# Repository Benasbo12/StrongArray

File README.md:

# StrongArray
Strong array schematics and programs for use with MSc by research thesis - Benjamin Astbury

PySweeperGUI - ArduinoRev4 for use with controlling Raspberry Pi

Switch4x4 for uploading to Arduino Due

Eagle Schematics and board for production and fitting to top of Arduino Due as specified in Thesis

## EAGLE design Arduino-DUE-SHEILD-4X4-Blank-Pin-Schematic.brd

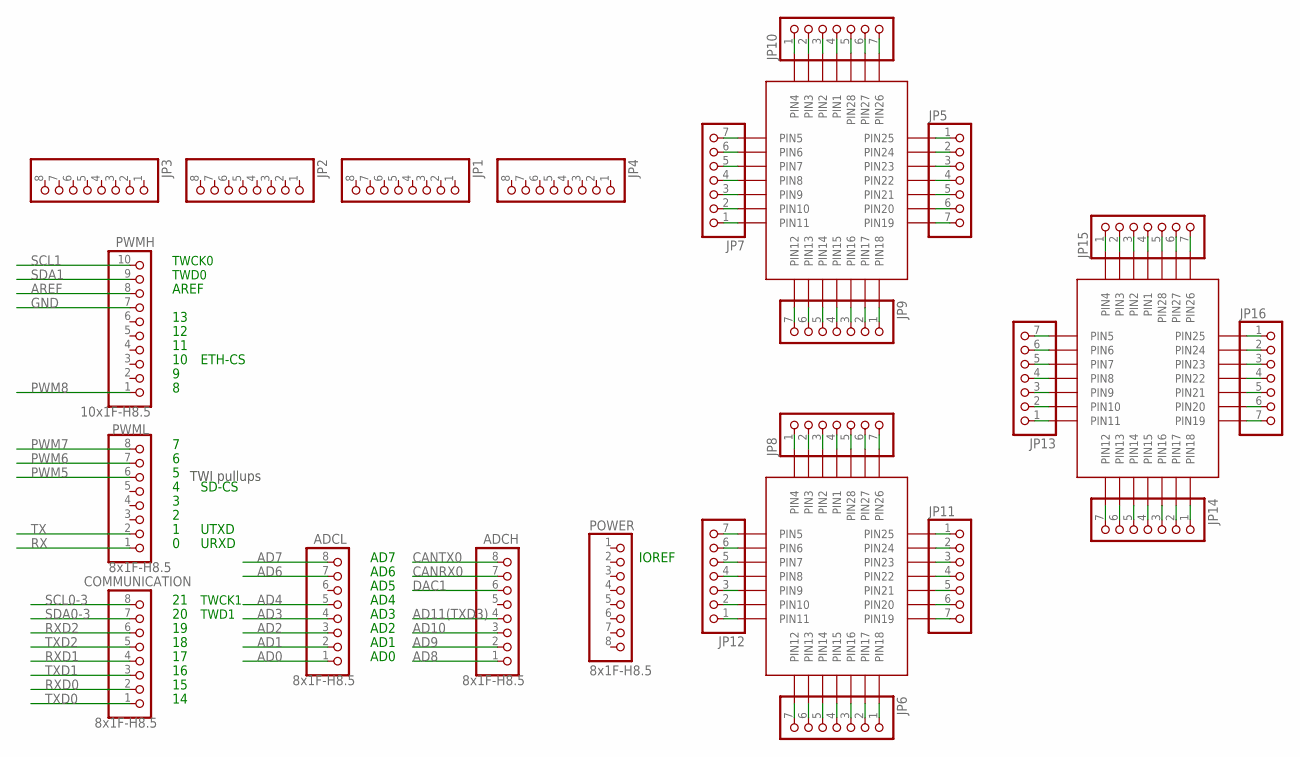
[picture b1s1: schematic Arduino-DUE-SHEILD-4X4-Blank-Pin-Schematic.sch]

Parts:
ADCH: 8x1F-H8.5; 1X08
ADCL: 8x1F-H8.5; 1X08
COMMUNICATION: 8x1F-H8.5; 1X08
JP1, JP2, JP3, JP4: PINHD-1X8; 1X08
JP5, JP6, JP7, JP8, JP9, JP10, JP11, JP12, JP13, JP14, JP15, JP16: PINHD-1X7; 1X07
POWER: 8x1F-H8.5; 1X08
PWMH: 10x1F-H8.5; 1X10
PWML: 8x1F-H8.5; 1X08
U$1, U$2, U$3: S28

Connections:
AD0: ADCL.1
AD1: ADCL.2
AD2: ADCL.3
AD3: ADCL.4
AD4: ADCL.5
AD6: ADCL.7
AD7: ADCL.8
AD8: ADCH.1
AD9: ADCH.2
AD10: ADCH.3
AD11(TXD3): ADCH.4
AREF: PWMH.8
CANRX0: ADCH.7
CANTX0: ADCH.8
DAC1: ADCH.6
GND: PWMH.7
unnamed: JP7.7, U$1.5 (PIN5)
unnamed: JP7.6, U$1.6 (PIN6)
unnamed: JP7.5, U$1.7 (PIN7)
unnamed: JP7.4, U$1.8 (PIN8)
unnamed: JP7.3, U$1.9 (PIN9)
unnamed: JP7.2, U$1.10 (PIN10)
unnamed: JP7.1, U$1.11 (PIN11)
unnamed: JP9.7, U$1.12 (PIN12)
unnamed: JP9.6, U$1.13 (PIN13)
unnamed: JP9.5, U$1.14 (PIN14)
unnamed: JP9.4, U$1.15 (PIN15)
unnamed: JP9.3, U$1.16 (PIN16)
unnamed: JP9.2, U$1.17 (PIN17)
unnamed: JP9.1, U$1.18 (PIN18)
unnamed: JP5.7, U$1.19 (PIN19)
unnamed: JP5.6, U$1.20 (PIN20)
unnamed: JP5.5, U$1.21 (PIN21)
unnamed: JP5.4, U$1.22 (PIN22)
unnamed: JP5.3, U$1.23 (PIN23)
unnamed: JP5.2, U$1.24 (PIN24)
unnamed: JP5.1, U$1.25 (PIN25)
unnamed: JP10.1, U$1.4 (PIN4)
unnamed: JP10.2, U$1.3 (PIN3)
unnamed: JP10.3, U$1.2 (PIN2)
unnamed: JP10.4, U$1.1 (PIN1)
unnamed: JP10.5, U$1.28 (PIN28)
unnamed: JP10.6, U$1.27 (PIN27)
unnamed: JP10.7, U$1.26 (PIN26)
unnamed: JP8.1, U$2.4 (PIN4)
unnamed: JP8.2, U$2.3 (PIN3)
unnamed: JP8.3, U$2.2 (PIN2)
unnamed: JP8.4, U$2.1 (PIN1)
unnamed: JP8.5, U$2.28 (PIN28)
unnamed: JP8.6, U$2.27 (PIN27)
unnamed: JP8.7, U$2.26 (PIN26)
unnamed: JP13.7, U$3.5 (PIN5)
unnamed: JP13.6, U$3.6 (PIN6)
unnamed: JP13.5, U$3.7 (PIN7)
unnamed: JP13.4, U$3.8 (PIN8)
unnamed: JP13.3, U$3.9 (PIN9)
unnamed: JP13.2, U$3.10 (PIN10)
unnamed: JP13.1, U$3.11 (PIN11)
unnamed: JP6.7, U$2.12 (PIN12)
unnamed: JP6.6, U$2.13 (PIN13)
unnamed: JP6.5, U$2.14 (PIN14)
unnamed: JP6.4, U$2.15 (PIN15)
unnamed: JP6.3, U$2.16 (PIN16)
unnamed: JP6.2, U$2.17 (PIN17)
unnamed: JP6.1, U$2.18 (PIN18)
unnamed: JP11.7, U$2.19 (PIN19)
unnamed: JP11.6, U$2.20 (PIN20)
unnamed: JP11.5, U$2.21 (PIN21)
unnamed: JP11.4, U$2.22 (PIN22)
unnamed: JP11.3, U$2.23 (PIN23)
unnamed: JP11.2, U$2.24 (PIN24)
unnamed: JP11.1, U$2.25 (PIN25)
unnamed: JP12.7, U$2.5 (PIN5)
unnamed: JP12.6, U$2.6 (PIN6)
unnamed: JP12.5, U$2.7 (PIN7)
unnamed: JP12.4, U$2.8 (PIN8)
unnamed: JP12.3, U$2.9 (PIN9)
unnamed: JP12.2, U$2.10 (PIN10)
unnamed: JP12.1, U$2.11 (PIN11)
unnamed: JP15.1, U$3.4 (PIN4)
unnamed: JP15.2, U$3.3 (PIN3)
unnamed: JP15.3, U$3.2 (PIN2)
unnamed: JP15.4, U$3.1 (PIN1)
unnamed: JP15.5, U$3.28 (PIN28)
unnamed: JP15.6, U$3.27 (PIN27)
unnamed: JP15.7, U$3.26 (PIN26)
unnamed: JP16.1, U$3.25 (PIN25)
unnamed: JP16.2, U$3.24 (PIN24)
unnamed: JP16.3, U$3.23 (PIN23)
unnamed: JP16.4, U$3.22 (PIN22)
unnamed: JP16.5, U$3.21 (PIN21)
unnamed: JP16.6, U$3.20 (PIN20)
unnamed: JP16.7, U$3.19 (PIN19)
unnamed: JP14.1, U$3.18 (PIN18)
unnamed: JP14.2, U$3.17 (PIN17)
unnamed: JP14.3, U$3.16 (PIN16)
unnamed: JP14.4, U$3.15 (PIN15)
unnamed: JP14.5, U$3.14 (PIN14)
unnamed: JP14.6, U$3.13 (PIN13)
unnamed: JP14.7, U$3.12 (PIN12)
PWM5: PWML.6
PWM6: PWML.7
PWM7: PWML.8
PWM8: PWMH.1
RX: PWML.1
RXD0: COMMUNICATION.2
RXD1: COMMUNICATION.4
RXD2: COMMUNICATION.6
SCL0-3: COMMUNICATION.8
SCL1: PWMH.10
SDA0-3: COMMUNICATION.7
SDA1: PWMH.9
TX: PWML.2
TXD0: COMMUNICATION.1
TXD1: COMMUNICATION.3
TXD2: COMMUNICATION.5

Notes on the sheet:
TWI pullups
TWCK1
TWD1
IOREF
TWCK0
TWD0
AD1
AD2
AD3
AD4
AD5
AD6
AD0
AREF
AD7
SD-CS
UTXD
URXD
ETH-CS

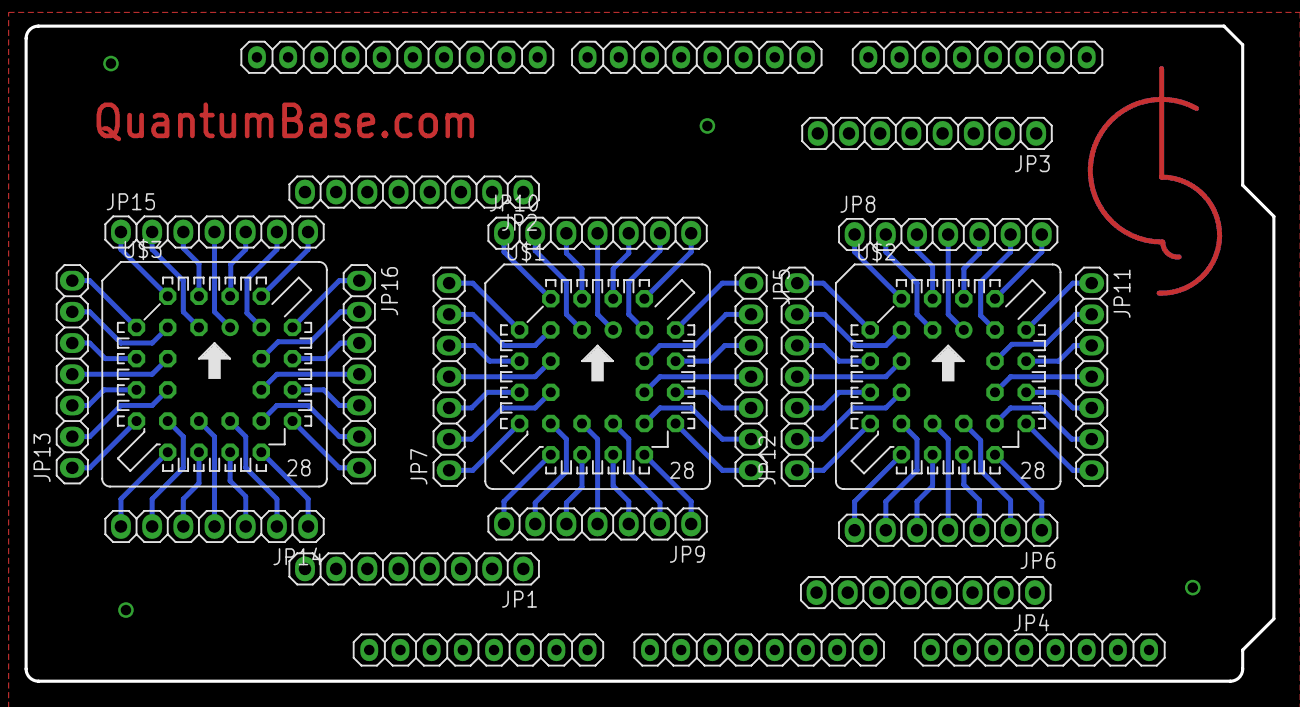
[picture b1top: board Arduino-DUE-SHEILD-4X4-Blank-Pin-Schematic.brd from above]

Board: 2 copper layers, 101.6 x 53.3 mm, 25 parts (0 on the bottom side), 84 nets.

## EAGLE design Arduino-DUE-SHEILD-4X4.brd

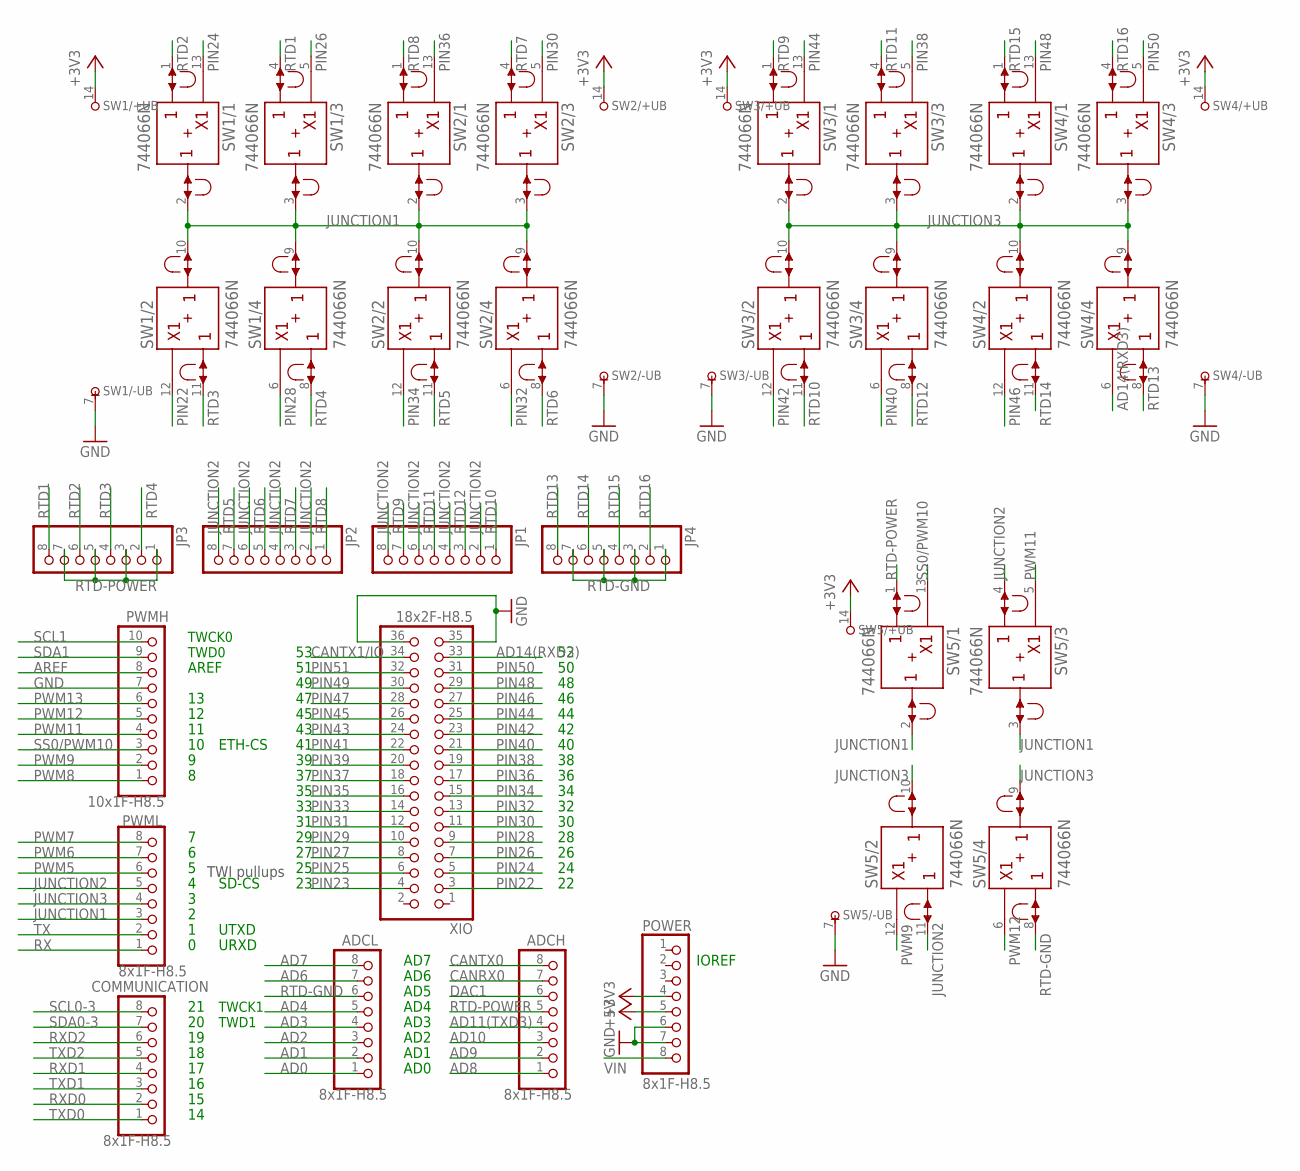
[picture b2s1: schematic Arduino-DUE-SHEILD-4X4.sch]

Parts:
ADCH: 8x1F-H8.5; 1X08
ADCL: 8x1F-H8.5; 1X08
COMMUNICATION: 8x1F-H8.5; 1X08
JP1, JP2, JP3, JP4: PINHD-1X8; 1X08
POWER: 8x1F-H8.5; 1X08
PWMH: 10x1F-H8.5; 1X10
PWML: 8x1F-H8.5; 1X08
SW1, SW2, SW3, SW4, SW5: 744066N; DIL14
XIO: 18x2F-H8.5; 2X18

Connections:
+3V3: POWER.4, SW1.14 (+UB), SW2.14 (+UB), SW3.14 (+UB), SW4.14 (+UB), SW5.14 (+UB)
+5V: POWER.5
AD0: ADCL.1
AD1: ADCL.2
AD2: ADCL.3
AD3: ADCL.4
AD4: ADCL.5
AD6: ADCL.7
AD7: ADCL.8
AD8: ADCH.1
AD9: ADCH.2
AD10: ADCH.3
AD11(TXD3): ADCH.4
AD14(RXD3): SW4.6 (C), XIO.33
AREF: PWMH.8
CANRX0: ADCH.7
CANTX0: ADCH.8
CANTX1/IO: XIO.34
DAC1: ADCH.6
GND: POWER.6, POWER.7, PWMH.7, SW1.7 (-UB), SW2.7 (-UB), SW3.7 (-UB), SW4.7 (-UB), SW5.7 (-UB), XIO.35, XIO.36
JUNCTION1: PWML.3, SW1.2 (B), SW1.3 (B), SW1.9 (B), SW1.10 (B), SW2.2 (B), SW2.3 (B), SW2.9 (B), SW2.10 (B), SW5.2 (B), SW5.3 (B)
JUNCTION2: JP1.2, JP1.4, JP1.6, JP1.8, JP2.2, JP2.4, JP2.6, JP2.8, PWML.5, SW5.4 (A), SW5.11 (A)
JUNCTION3: PWML.4, SW3.2 (B), SW3.3 (B), SW3.9 (B), SW3.10 (B), SW4.2 (B), SW4.3 (B), SW4.9 (B), SW4.10 (B), SW5.9 (B), SW5.10 (B)
PIN22: SW1.12 (C), XIO.3
PIN23: XIO.4
PIN24: SW1.13 (C), XIO.5
PIN25: XIO.6
PIN26: SW1.5 (C), XIO.7
PIN27: XIO.8
PIN28: SW1.6 (C), XIO.9
PIN29: XIO.10
PIN30: SW2.5 (C), XIO.11
PIN31: XIO.12
PIN32: SW2.6 (C), XIO.13
PIN33: XIO.14
PIN34: SW2.12 (C), XIO.15
PIN35: XIO.16
PIN36: SW2.13 (C), XIO.17
PIN37: XIO.18
PIN38: SW3.5 (C), XIO.19
PIN39: XIO.20
PIN40: SW3.6 (C), XIO.21
PIN41: XIO.22
PIN42: SW3.12 (C), XIO.23
PIN43: XIO.24
PIN44: SW3.13 (C), XIO.25
PIN45: XIO.26
PIN46: SW4.12 (C), XIO.27
PIN47: XIO.28
PIN48: SW4.13 (C), XIO.29
PIN49: XIO.30
PIN50: SW4.5 (C), XIO.31
PIN51: XIO.32
PWM5: PWML.6
PWM6: PWML.7
PWM7: PWML.8
PWM8: PWMH.1
PWM9: PWMH.2, SW5.12 (C)
PWM11: PWMH.4, SW5.5 (C)
PWM12: PWMH.5, SW5.6 (C)
PWM13: PWMH.6
RTD1: JP3.8, SW1.4 (A)
RTD2: JP3.6, SW1.1 (A)
RTD3: JP3.4, SW1.11 (A)
RTD4: JP3.2, SW1.8 (A)
RTD5: JP2.7, SW2.11 (A)
RTD6: JP2.5, SW2.8 (A)
RTD7: JP2.3, SW2.4 (A)
RTD8: JP2.1, SW2.1 (A)
RTD9: JP1.7, SW3.1 (A)
RTD10: JP1.1, SW3.11 (A)
RTD11: JP1.5, SW3.4 (A)
RTD12: JP1.3, SW3.8 (A)
RTD13: JP4.8, SW4.8 (A)
RTD14: JP4.6, SW4.11 (A)
RTD15: JP4.4, SW4.1 (A)
RTD16: JP4.2, SW4.4 (A)
RTD-GND: ADCL.6, JP4.1, JP4.3, JP4.5, JP4.7, SW5.8 (A)
RTD-POWER: ADCH.5, JP3.1, JP3.3, JP3.5, JP3.7, SW5.1 (A)
RX: PWML.1
RXD0: COMMUNICATION.2
RXD1: COMMUNICATION.4
RXD2: COMMUNICATION.6
SCL0-3: COMMUNICATION.8
SCL1: PWMH.10
SDA0-3: COMMUNICATION.7
SDA1: PWMH.9
SS0/PWM10: PWMH.3, SW5.13 (C)
TX: PWML.2
TXD0: COMMUNICATION.1
TXD1: COMMUNICATION.3
TXD2: COMMUNICATION.5
VIN: POWER.8

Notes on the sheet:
TWI pullups
TWCK1
TWD1
IOREF
TWCK0
TWD0
AD1
AD2
AD3
AD4
AD5
AD6
AD0
AREF
AD7
SD-CS
UTXD
URXD
ETH-CS

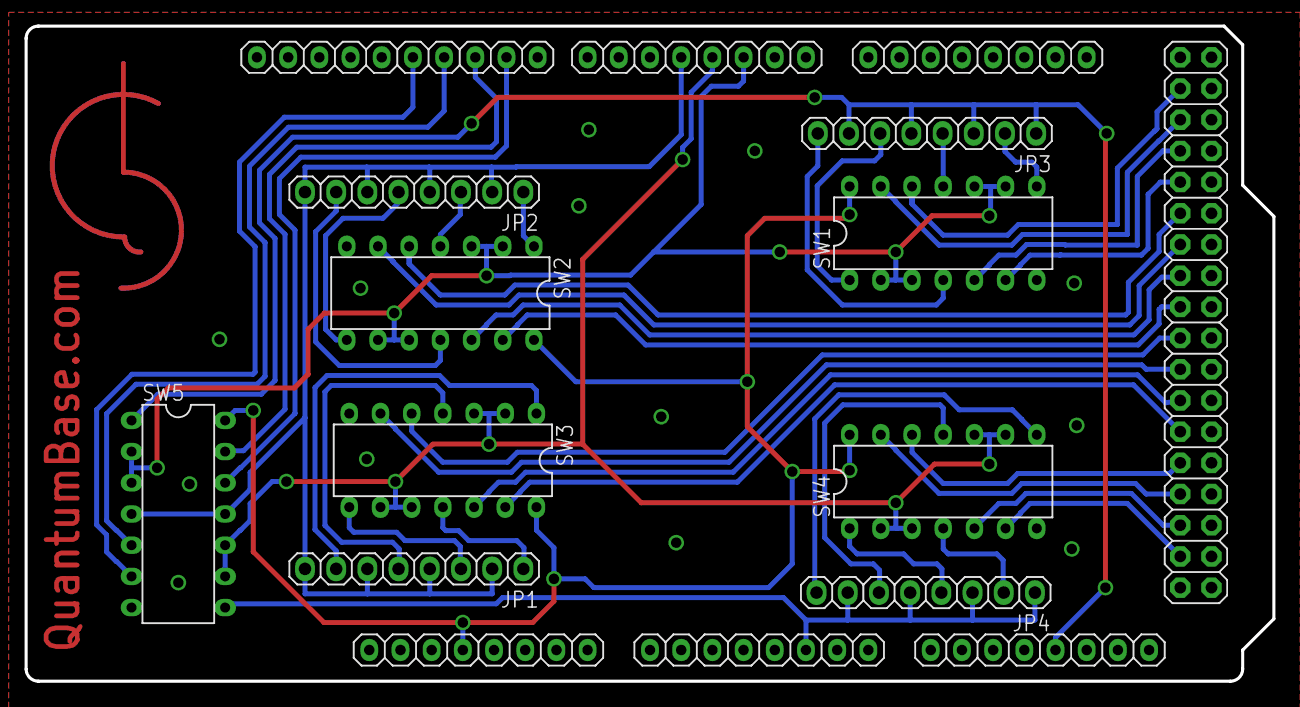
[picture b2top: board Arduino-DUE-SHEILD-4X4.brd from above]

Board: 2 copper layers, 101.6 x 53.3 mm, 16 parts (0 on the bottom side), 43 nets.
